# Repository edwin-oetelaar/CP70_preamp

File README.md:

# Yamaha CP70 Electric Grand Piano - 72 Channel Pre-amplifier Project

https://www.pomeindhoven.nl/

Paviljoen Ongehoorde Muziek
Vestdijk 25 - 5611 CA
Eindhoven

## Project Overview

This repository contains the KiCad project files, documentation, and design decisions for a custom-built 72-channel pre-amplifier designed for a Yamaha CP70 electric grand piano. This project is an open-source initiative developed in collaboration with [Paviljoen Ongehoorde Muziek (POM)](https://www.pomeindhoven.nl/) in Eindhoven, Netherlands, as part of an art project.

The primary goal of this pre-amplifier is to individually buffer and potentially amplify the signals from each of the 72 string pickups of the CP70, providing a high-quality, low-noise output output signal for further amplification to 72 speakers.

**Repository URL:** [https://github.com/edwin-oetelaar/CP70_preamp/tree/main](https://github.com/edwin-oetelaar/CP70_preamp/tree/main)

## Image of the piano

## Background

The Yamaha CP70 is an iconic electric grand piano known for its unique sound, derived from real strings and hammers combined with a piezo pickup system.
This project aims to provide a modern, high-fidelity replacement, with 72 separate output channels as an alternative pre-amplifier system.

This pre-amp is designed with the following considerations:
*   **High Input Impedance:** To accurately capture the full tonal character of the CP70 pickups without loading them down.
*   **Low Noise Performance:** Essential for a clean signal, especially with 72 individual channels.
*   **Sufficient Headroom:** To handle the potentially large signal swings from the pickups.
*   **Individual Channel Processing:** Each pickup receives its own pre-amplifier stage.
*   **Modularity:** For ease of assembly, testing, and maintenance.
*   **Open Source:** All design files and documentation are publicly available to encourage learning, modification, accessibility.

## Project Status

[ **TODO: Update this section regularly, e.g., In Design, Prototyping, Tested, In Use** ]

*   Current Version: [e.g., v0.1 - Initial Design]
*   Key Milestones:
    *   [x] Initial schematic design complete.
    *   [x] PCB layout for [16]-channel module complete.
    *   [x] PCB ordered
    *   [x] parts ordered
    *   [ ] First prototype(s) built and tested.
    *   [ ] Full 72-channel system assembled.
    *   [ ] Integration with the CP70 at Paviljoen Ongehoorde Muziek.

## Design Files and Documentation

This repository is structured to include:

*   **/kicad_project:** Contains the KiCad schematic and PCB layout files.
    *   `CP70_preamp.kicad_pro` - Main KiCad project file.
    *   `CP70_preamp.kicad_sch` - Main schematic file.
    *   `CP70_preamp.kicad_pcb` - Main PCB layout file (or individual module files).
    *   `libraries/` - Custom schematic symbols and PCB footprints, if any.
    *   `out1/` - Gerber files for PCB manufacturing (to be added when ready). (file out1.zip sent to JLCPCB)
    *   `bom/` - Bill of Materials (to be added).
*   **/documentation:**
    *   `design_decisions.md` - Detailed explanation of the design choices, component selection, and rationale.
    *   `specifications.md` - Target specifications for the pre-amplifier.
    *   `testing_procedure.md` - (To be added) How to test individual modules and the full system.
    *   Images, block diagrams, and other supporting documents.
*   **/images:** Schematics, photos of prototypes, etc.
*   `README.md` - This file.

# image of version 0.1 printed circuit board

## Key Design Aspects (Summary)

*   **Number of Channels:** 72 (one for each pickup)
*   **Input Stage:** High-impedance buffer for each channel.
    *   Target Input Impedance: 470K Ω
    *   Expected Pickup Output: Up to 45V peak-to-peak in 1 M (requiring input attenuation).
*   **Operational Amplifier:** [e.g., TL072 or similar, specify your choice and link to design_decisions.md]
*   **Power Supply:** Symmetrical (e.g., +/-15V or +/-18V)
*   **Gain:** [e.g., Unity gain buffer, or variable gain via potentiometer - specify and link to design_decisions.md]

More detailed information on architecture, component choices, and trade-offs can be found in `/documentation/design_decisions.md`.

## Getting Started / How to Use

1.  **Clone the repository:**
    ```bash
    git clone https://github.com/edwin-oetelaar/CP70_preamp.git
    cd CP70_preamp
    ```
2.  **Open in KiCad:** Open the `CP70_preamp.kicad_pro` file in KiCad (Latest version).
3.  **Review Schematics and PCB Layout:** Explore the design in the KiCad schematic editor and PCB editor.
4.  **Check Documentation:** Read through the `design_decisions.md` and other documents for a deeper understanding.

## Contributing

This is an open-source project, and contributions or suggestions are welcome! If you have ideas, find bugs, or want to contribute to the design:

1.  **Fork the repository.**
2.  **Create a new branch** for your feature or bug fix.
3.  **Make your changes.**
4.  **Submit a Pull Request** with a clear description of your changes.

You can also open an [Issue](https://github.com/edwin-oetelaar/CP70_preamp/issues) to report bugs or suggest improvements.

## Collaboration

This project is in proud collaboration with:

**Paviljoen Ongehoorde Muziek (POM)**
Vestdijk 25 - 5611 CA Eindhoven
[https://www.pomeindhoven.nl/](https://www.pomeindhoven.nl/)

The pre-amplifier is intended for use in an art project hosted at POM.

## License

This project is licensed under the [MIT License](LICENSE.md) - see the LICENSE.md file for details.

## Contact

For questions or discussions regarding this project, you can contact:
*   Edwin van den Oetelaar - Leave a message in the issue tracker or google my name/email 
*   Or open an issue on this GitHub repository.

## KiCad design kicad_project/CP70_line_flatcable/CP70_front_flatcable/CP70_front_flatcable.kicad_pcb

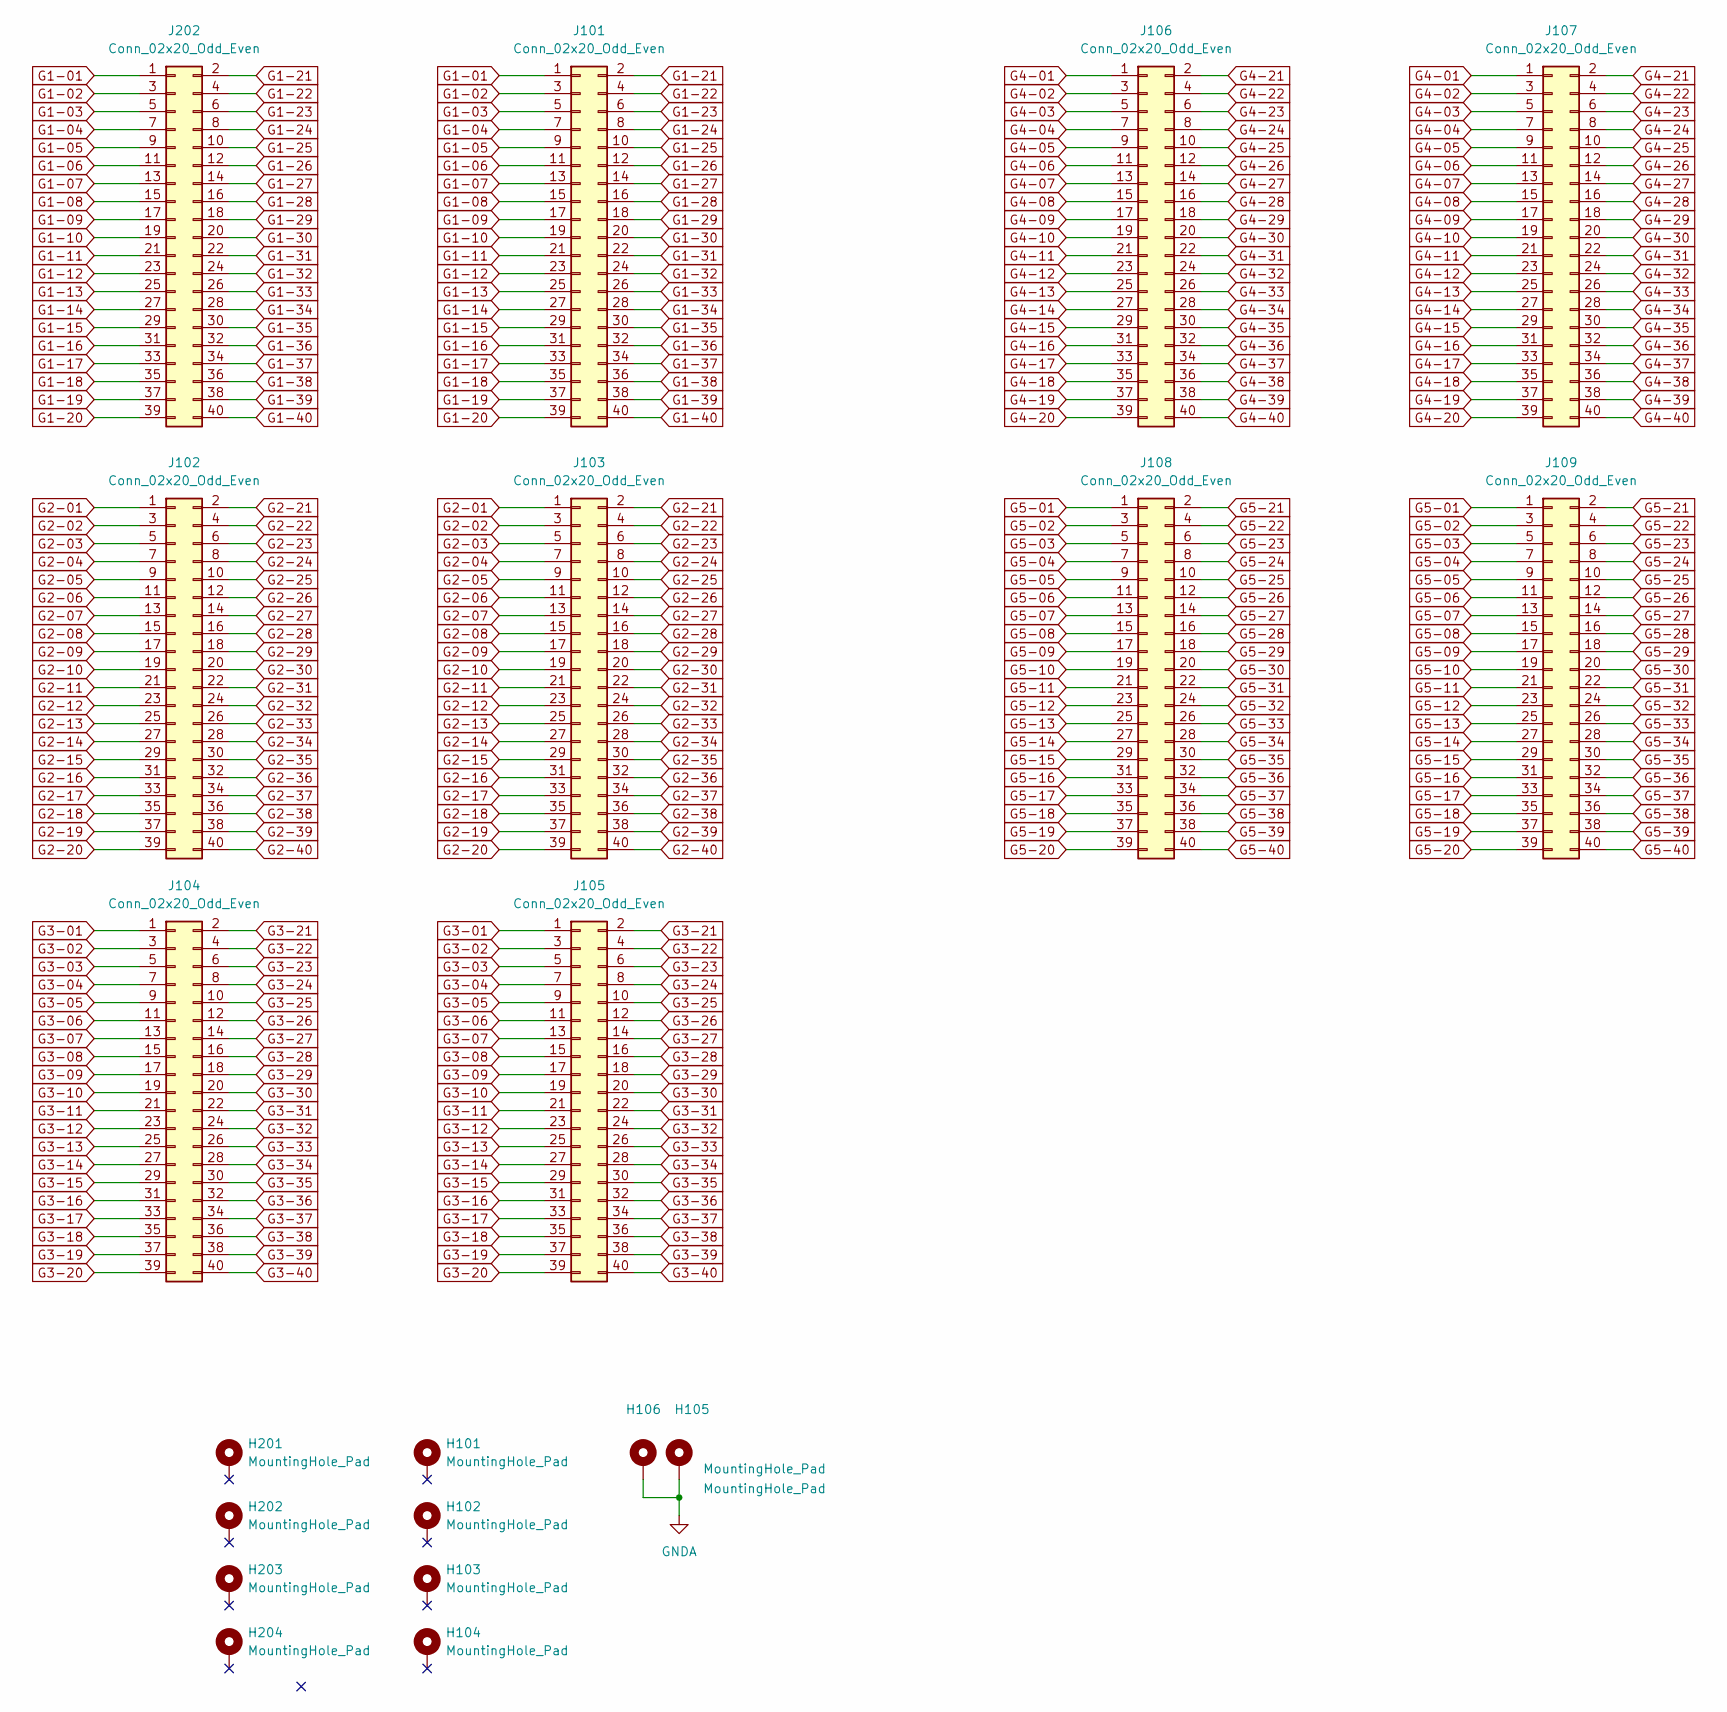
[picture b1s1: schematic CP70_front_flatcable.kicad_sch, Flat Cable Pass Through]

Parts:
H101, H102, H103, H104, H105, H106, H201, H202, H203, H204: MountingHole_Pad; MountingHole_3.2mm_M3_Pad_Via
J101, J102, J103, J104, J105, J106, J107, J108, J109, J202: Conn_02x20_Odd_Even; IDC-Header_2x20-1MP_P2.54mm_Latch9.5mm_Vertical

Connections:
G1-01: J101.1, J202.1
G1-02: J101.3, J202.3
G1-03: J101.5, J202.5
G1-04: J101.7, J202.7
G1-05: J101.9, J202.9
G1-06: J101.11, J202.11
G1-07: J101.13, J202.13
G1-08: J101.15, J202.15
G1-09: J101.17, J202.17
G1-10: J101.19, J202.19
G1-11: J101.21, J202.21
G1-12: J101.23, J202.23
G1-13: J101.25, J202.25
G1-14: J101.27, J202.27
G1-15: J101.29, J202.29
G1-16: J101.31, J202.31
G1-17: J101.33, J202.33
G1-18: J101.35, J202.35
G1-19: J101.37, J202.37
G1-20: J101.39, J202.39
G1-21: J101.2, J202.2
G1-22: J101.4, J202.4
G1-23: J101.6, J202.6
G1-24: J101.8, J202.8
G1-25: J101.10, J202.10
G1-26: J101.12, J202.12
G1-27: J101.14, J202.14
G1-28: J101.16, J202.16
G1-29: J101.18, J202.18
G1-30: J101.20, J202.20
G1-31: J101.22, J202.22
G1-32: J101.24, J202.24
G1-33: J101.26, J202.26
G1-34: J101.28, J202.28
G1-35: J101.30, J202.30
G1-36: J101.32, J202.32
G1-37: J101.34, J202.34
G1-38: J101.36, J202.36
G1-39: J101.38, J202.38
G1-40: J101.40, J202.40
G2-01: J102.1, J103.1
G2-02: J102.3, J103.3
G2-03: J102.5, J103.5
G2-04: J102.7, J103.7
G2-05: J102.9, J103.9
G2-06: J102.11, J103.11
G2-07: J102.13, J103.13
G2-08: J102.15, J103.15
G2-09: J102.17, J103.17
G2-10: J102.19, J103.19
G2-11: J102.21, J103.21
G2-12: J102.23, J103.23
G2-13: J102.25, J103.25
G2-14: J102.27, J103.27
G2-15: J102.29, J103.29
G2-16: J102.31, J103.31
G2-17: J102.33, J103.33
G2-18: J102.35, J103.35
G2-19: J102.37, J103.37
G2-20: J102.39, J103.39
G2-21: J102.2, J103.2
G2-22: J102.4, J103.4
G2-23: J102.6, J103.6
G2-24: J102.8, J103.8
G2-25: J102.10, J103.10
G2-26: J102.12, J103.12
G2-27: J102.14, J103.14
G2-28: J102.16, J103.16
G2-29: J102.18, J103.18
G2-30: J102.20, J103.20
G2-31: J102.22, J103.22
G2-32: J102.24, J103.24
G2-33: J102.26, J103.26
G2-34: J102.28, J103.28
G2-35: J102.30, J103.30
G2-36: J102.32, J103.32
G2-37: J102.34, J103.34
G2-38: J102.36, J103.36
G2-39: J102.38, J103.38
G2-40: J102.40, J103.40
G3-01: J104.1, J105.1
G3-02: J104.3, J105.3
G3-03: J104.5, J105.5
G3-04: J104.7, J105.7
G3-05: J104.9, J105.9
G3-06: J104.11, J105.11
G3-07: J104.13, J105.13
G3-08: J104.15, J105.15
G3-09: J104.17, J105.17
G3-10: J104.19, J105.19
G3-11: J104.21, J105.21
G3-12: J104.23, J105.23
G3-13: J104.25, J105.25
G3-14: J104.27, J105.27
G3-15: J104.29, J105.29
G3-16: J104.31, J105.31
G3-17: J104.33, J105.33
G3-18: J104.35, J105.35
G3-19: J104.37, J105.37
G3-20: J104.39, J105.39
G3-21: J104.2, J105.2
G3-22: J104.4, J105.4
G3-23: J104.6, J105.6
G3-24: J104.8, J105.8
G3-25: J104.10, J105.10
G3-26: J104.12, J105.12
G3-27: J104.14, J105.14
G3-28: J104.16, J105.16
G3-29: J104.18, J105.18
G3-30: J104.20, J105.20
G3-31: J104.22, J105.22
G3-32: J104.24, J105.24
G3-33: J104.26, J105.26
G3-34: J104.28, J105.28
G3-35: J104.30, J105.30
G3-36: J104.32, J105.32
G3-37: J104.34, J105.34
G3-38: J104.36, J105.36
G3-39: J104.38, J105.38
G3-40: J104.40, J105.40
G4-01: J106.1, J107.1
G4-02: J106.3, J107.3
G4-03: J106.5, J107.5
G4-04: J106.7, J107.7
G4-05: J106.9, J107.9
G4-06: J106.11, J107.11
G4-07: J106.13, J107.13
G4-08: J106.15, J107.15
G4-09: J106.17, J107.17
G4-10: J106.19, J107.19
G4-11: J106.21, J107.21
G4-12: J106.23, J107.23
G4-13: J106.25, J107.25
G4-14: J106.27, J107.27
G4-15: J106.29, J107.29
G4-16: J106.31, J107.31
G4-17: J106.33, J107.33
G4-18: J106.35, J107.35
G4-19: J106.37, J107.37
G4-20: J106.39, J107.39
G4-21: J106.2, J107.2
G4-22: J106.4, J107.4
G4-23: J106.6, J107.6
G4-24: J106.8, J107.8
G4-25: J106.10, J107.10
G4-26: J106.12, J107.12
G4-27: J106.14, J107.14
G4-28: J106.16, J107.16
G4-29: J106.18, J107.18
G4-30: J106.20, J107.20
G4-31: J106.22, J107.22
G4-32: J106.24, J107.24
G4-33: J106.26, J107.26
G4-34: J106.28, J107.28
G4-35: J106.30, J107.30
G4-36: J106.32, J107.32
G4-37: J106.34, J107.34
G4-38: J106.36, J107.36
G4-39: J106.38, J107.38
G4-40: J106.40, J107.40
G5-01: J108.1, J109.1
G5-02: J108.3, J109.3
G5-03: J108.5, J109.5
G5-04: J108.7, J109.7
G5-05: J108.9, J109.9
G5-06: J108.11, J109.11
G5-07: J108.13, J109.13
G5-08: J108.15, J109.15
G5-09: J108.17, J109.17
G5-10: J108.19, J109.19
G5-11: J108.21, J109.21
G5-12: J108.23, J109.23
G5-13: J108.25, J109.25
G5-14: J108.27, J109.27
G5-15: J108.29, J109.29
G5-16: J108.31, J109.31
G5-17: J108.33, J109.33
G5-18: J108.35, J109.35
G5-19: J108.37, J109.37
G5-20: J108.39, J109.39
G5-21: J108.2, J109.2
G5-22: J108.4, J109.4
G5-23: J108.6, J109.6
G5-24: J108.8, J109.8
G5-25: J108.10, J109.10
G5-26: J108.12, J109.12
G5-27: J108.14, J109.14
G5-28: J108.16, J109.16
G5-29: J108.18, J109.18
G5-30: J108.20, J109.20
G5-31: J108.22, J109.22
G5-32: J108.24, J109.24
G5-33: J108.26, J109.26
G5-34: J108.28, J109.28
G5-35: J108.30, J109.30
G5-36: J108.32, J109.32
G5-37: J108.34, J109.34
G5-38: J108.36, J109.36
G5-39: J108.38, J109.38
G5-40: J108.40, J109.40
GNDA: H105.1, H106.1

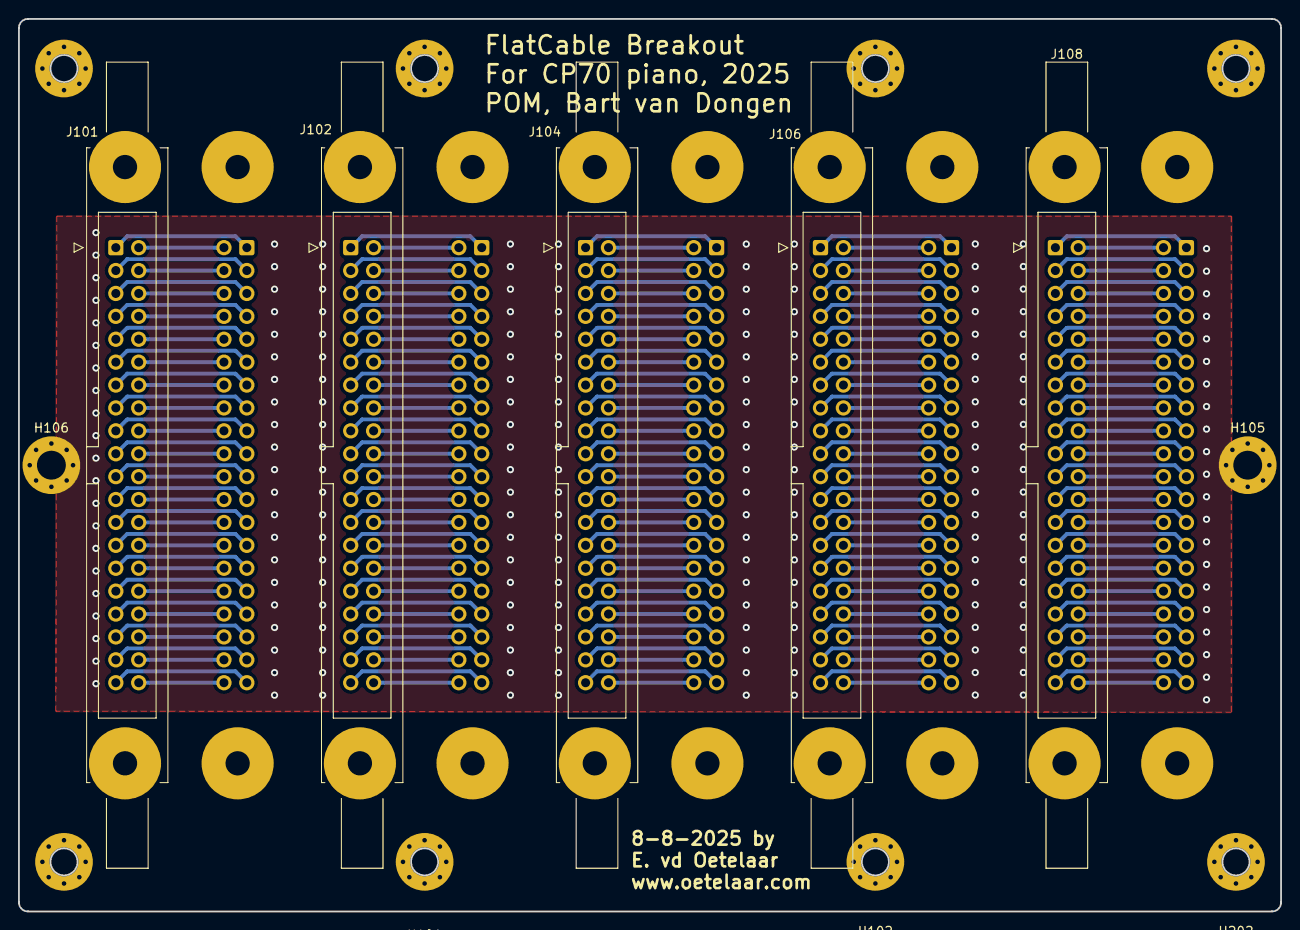
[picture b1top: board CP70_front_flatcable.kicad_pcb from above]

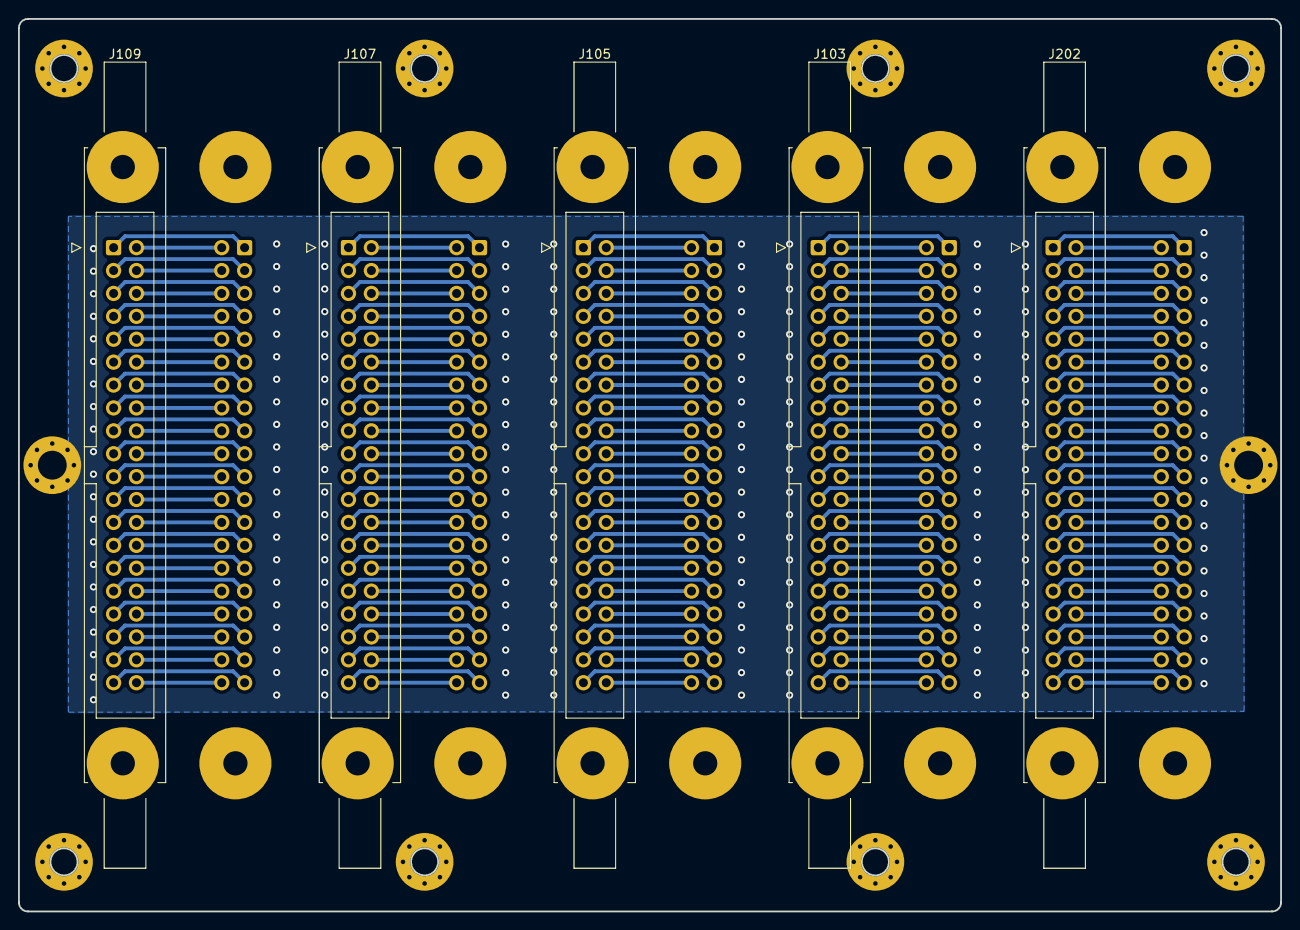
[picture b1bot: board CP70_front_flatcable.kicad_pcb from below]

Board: 2 copper layers, 140.0 x 99.0 mm, 20 parts (5 on the bottom side), 201 nets.

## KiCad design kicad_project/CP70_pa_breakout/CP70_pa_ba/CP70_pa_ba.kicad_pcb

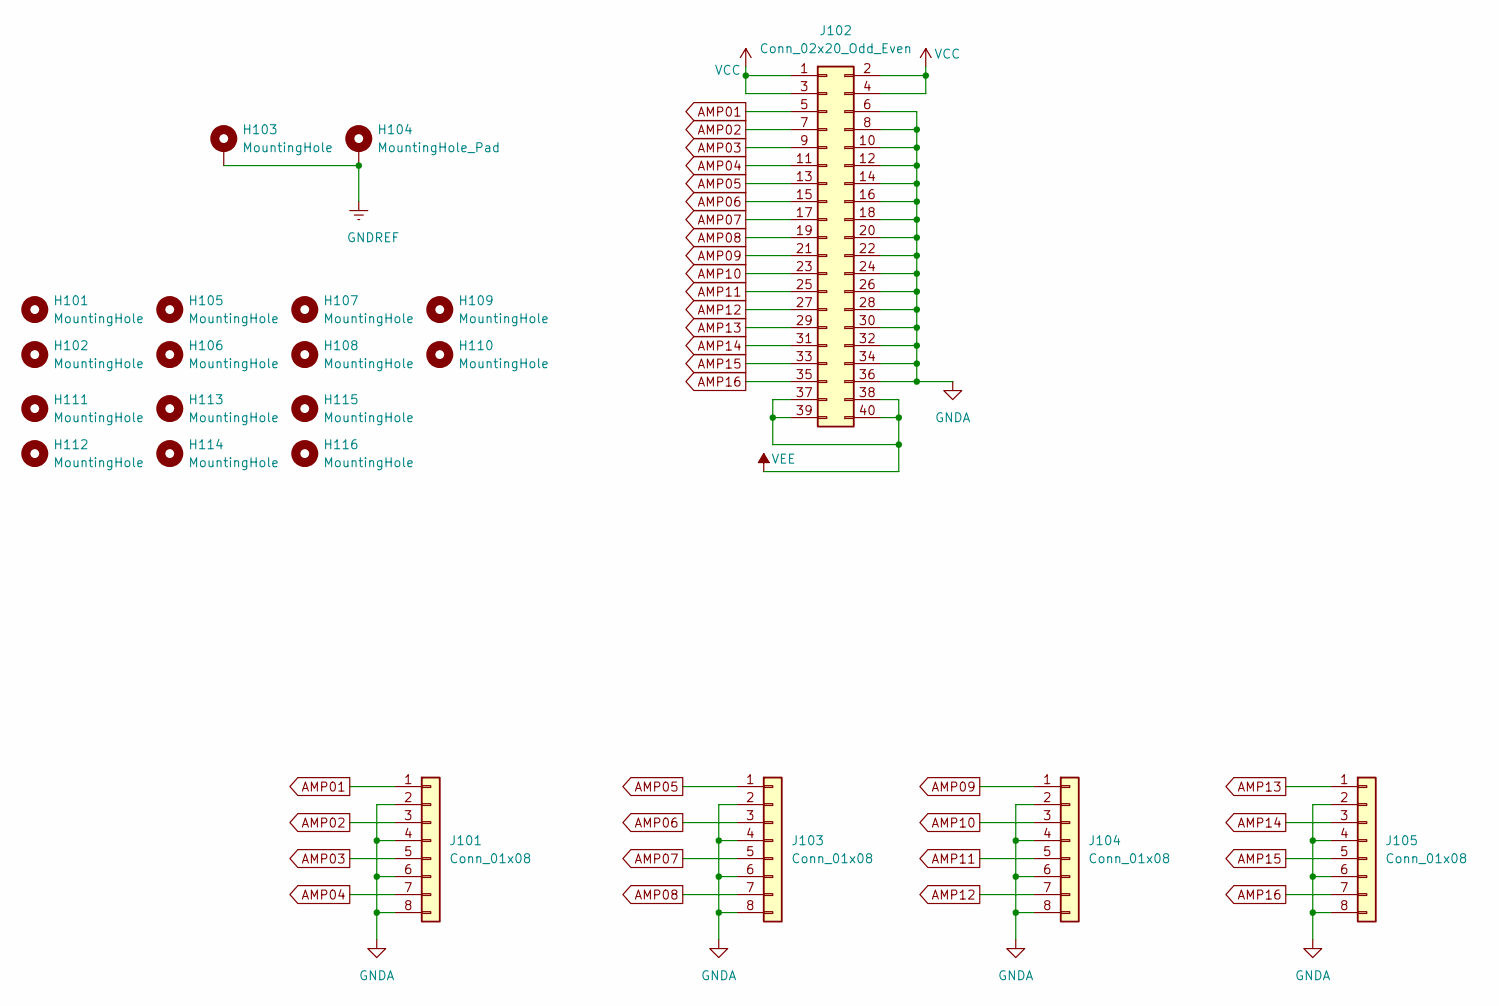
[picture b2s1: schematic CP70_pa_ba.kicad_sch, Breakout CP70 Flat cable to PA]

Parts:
H101, H102, H103, H105, H106, H107, H108, H109, H110, H111, H112, H113, H114, H115, H116: MountingHole; MountingHole_3.2mm_M3_Pad_Via
H104: MountingHole_Pad; MountingHole_3.2mm_M3_Pad_Via
J101, J103, J104, J105: Conn_01x08; KF141R-2.54-8
J102: Conn_02x20_Odd_Even; IDC-Header_2x20_P2.54mm_Latch_Vertical

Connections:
AMP01: J101.1, J102.5
AMP02: J101.3, J102.7
AMP03: J101.5, J102.9
AMP04: J101.7, J102.11
AMP05: J102.13, J103.1
AMP06: J102.15, J103.3
AMP07: J102.17, J103.5
AMP08: J102.19, J103.7
AMP09: J102.21, J104.1
AMP10: J102.23, J104.3
AMP11: J102.25, J104.5
AMP12: J102.27, J104.7
AMP13: J102.29, J105.1
AMP14: J102.31, J105.3
AMP15: J102.33, J105.5
AMP16: J102.35, J105.7
GNDA: J101.2, J101.4, J101.6, J101.8, J102.6, J102.8, J102.10, J102.12, J102.14, J102.16, J102.18, J102.20, J102.22, J102.24, J102.26, J102.28, J102.30, J102.32, J102.34, J102.36, J103.2, J103.4, J103.6, J103.8, J104.2, J104.4, J104.6, J104.8, J105.2, J105.4, J105.6, J105.8
GNDREF: H103.1, H104.1
VCC: J102.1, J102.2, J102.3, J102.4
VEE: J102.37, J102.38, J102.39, J102.40

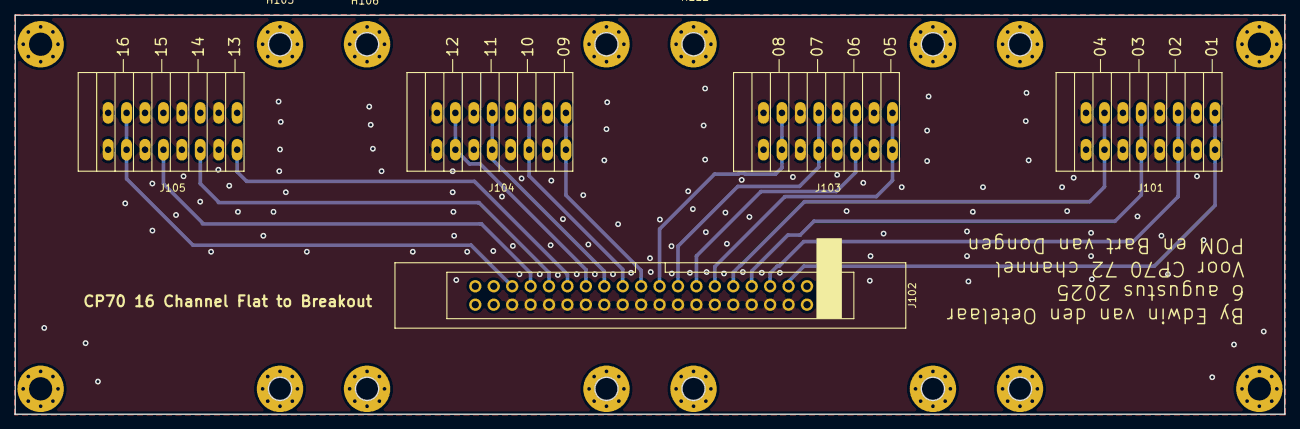
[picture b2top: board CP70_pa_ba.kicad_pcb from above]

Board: 2 copper layers, 175.0 x 55.0 mm, 21 parts (0 on the bottom side), 20 nets.

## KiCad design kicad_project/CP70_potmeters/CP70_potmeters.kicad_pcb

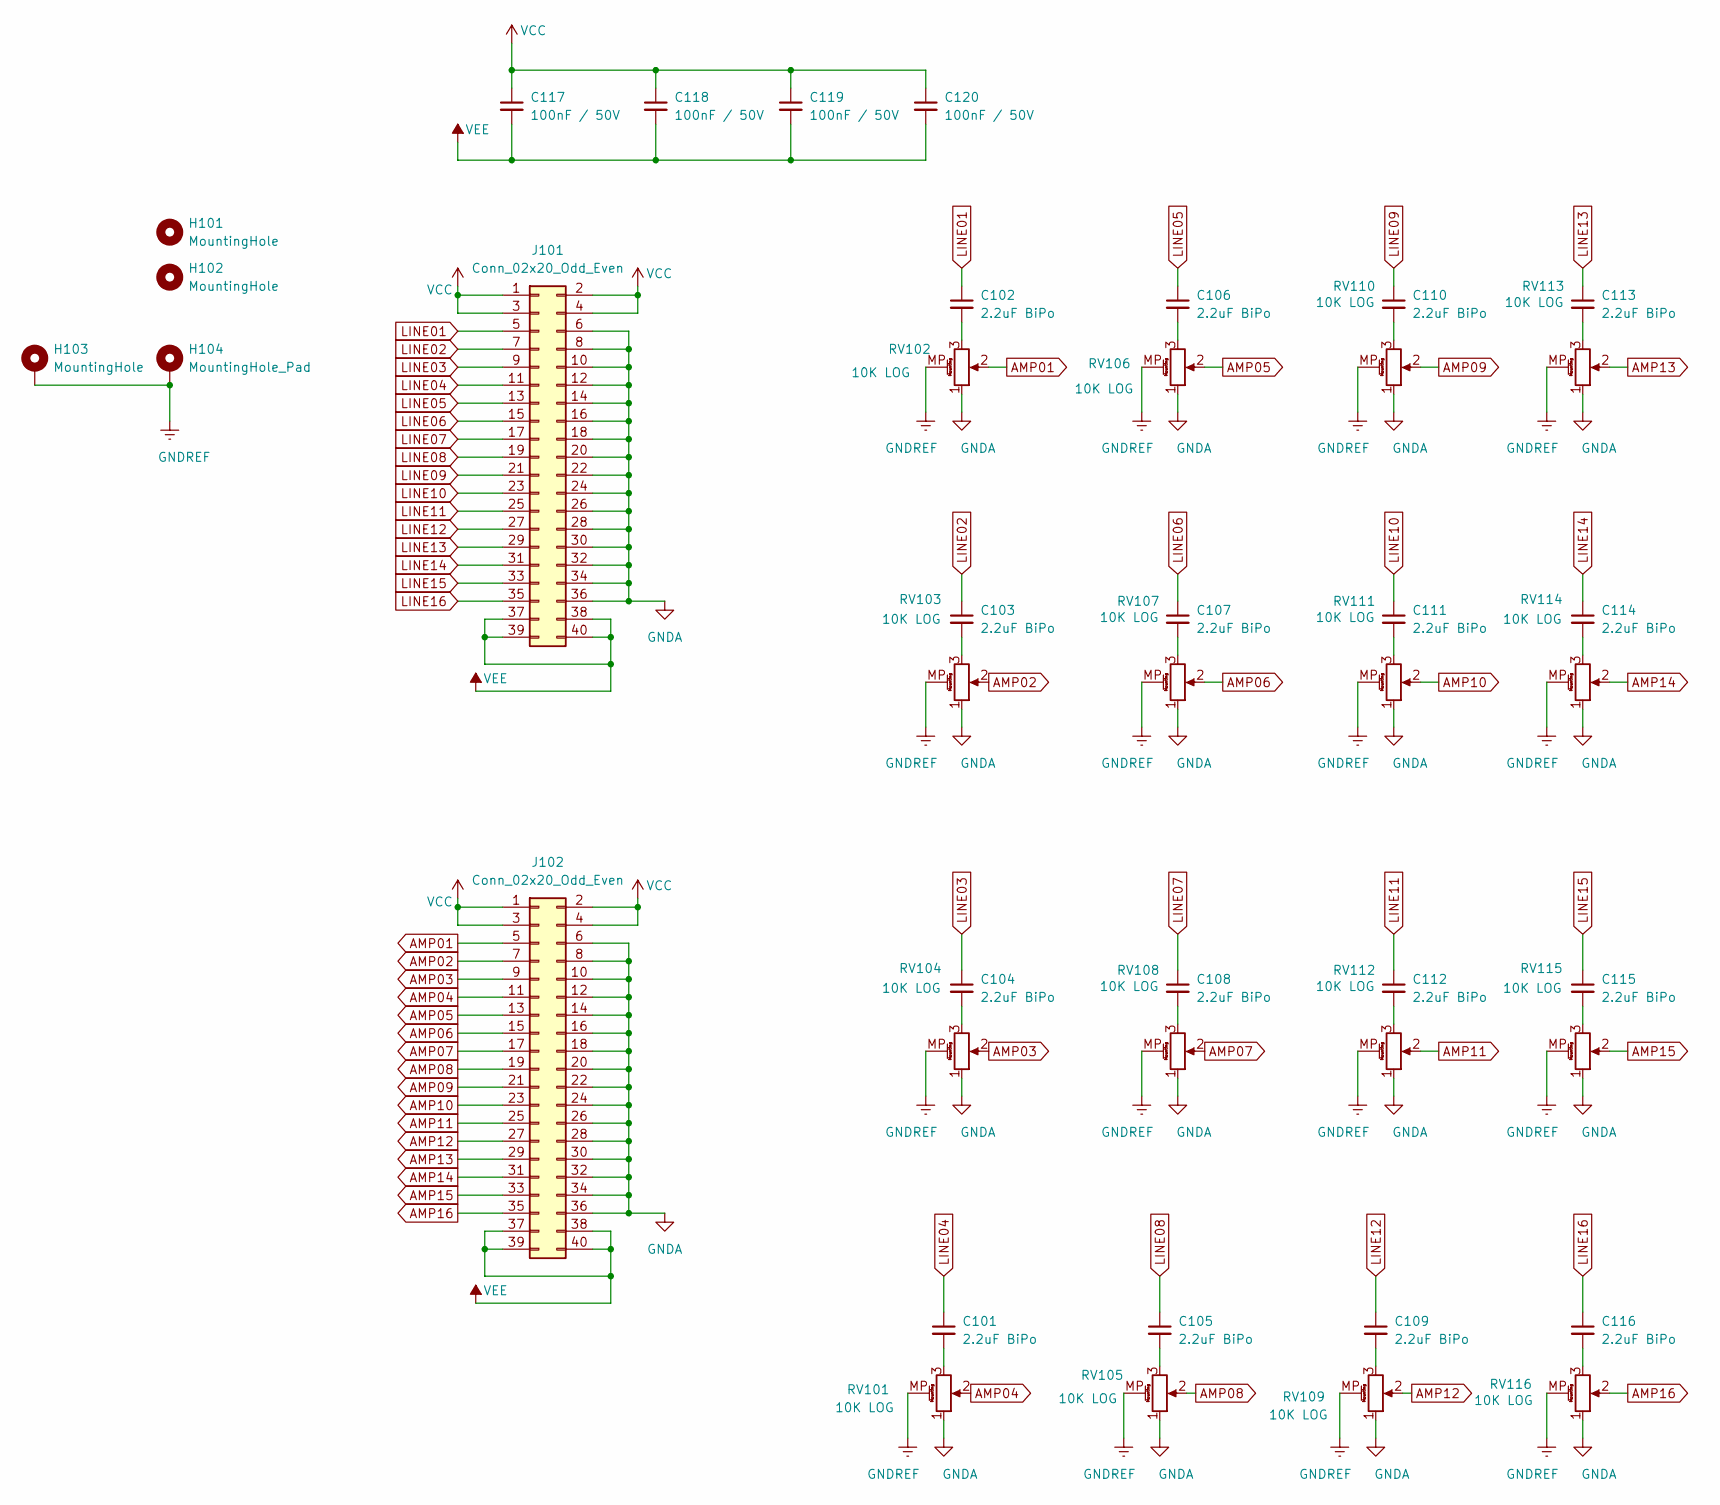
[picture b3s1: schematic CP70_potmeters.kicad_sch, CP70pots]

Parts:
C101, C102, C103, C104, C105, C106, C107, C108, C109, C110, C111, C112, C113, C114, C115, C116: 2.2uF BiPo; C_Radial_D5.0mm_H11.0mm_P2.00mm
C117, C118, C119, C120: 100nF / 50V; C_Disc_D6.0mm_W2.5mm_P5.00mm
H101, H102, H103: MountingHole; MountingHole_3.2mm_M3_Pad_Via
H104: MountingHole_Pad; MountingHole_3.2mm_M3_Pad_Via
J101, J102: Conn_02x20_Odd_Even; IDC-Header_2x20_P2.54mm_Latch_Vertical
RV101, RV102, RV103, RV104, RV105, RV106, RV107, RV108, RV109, RV110, RV111, RV112, RV113, RV114, RV115, RV116: 10K LOG; Potentiometer_Alps_RK09L_Single_Horizontal

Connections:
AMP01: J102.5, RV102.2
AMP02: J102.7, RV103.2
AMP03: J102.9, RV104.2
AMP04: J102.11, RV101.2
AMP05: J102.13, RV106.2
AMP06: J102.15, RV107.2
AMP07: J102.17, RV108.2
AMP08: J102.19, RV105.2
AMP09: J102.21, RV110.2
AMP10: J102.23, RV111.2
AMP11: J102.25, RV112.2
AMP12: J102.27, RV109.2
AMP13: J102.29, RV113.2
AMP14: J102.31, RV114.2
AMP15: J102.33, RV115.2
AMP16: J102.35, RV116.2
GNDA: J101.6, J101.8, J101.10, J101.12, J101.14, J101.16, J101.18, J101.20, J101.22, J101.24, J101.26, J101.28, J101.30, J101.32, J101.34, J101.36, J102.6, J102.8, J102.10, J102.12, J102.14, J102.16, J102.18, J102.20, J102.22, J102.24, J102.26, J102.28, J102.30, J102.32, J102.34, J102.36, RV101.1, RV102.1, RV103.1, RV104.1, RV105.1, RV106.1, RV107.1, RV108.1, RV109.1, RV110.1, RV111.1, RV112.1, RV113.1, RV114.1, RV115.1, RV116.1
GNDREF: H103.1, H104.1, RV101.MP (MountPin), RV102.MP (MountPin), RV103.MP (MountPin), RV104.MP (MountPin), RV105.MP (MountPin), RV106.MP (MountPin), RV107.MP (MountPin), RV108.MP (MountPin), RV109.MP (MountPin), RV110.MP (MountPin), RV111.MP (MountPin), RV112.MP (MountPin), RV113.MP (MountPin), RV114.MP (MountPin), RV115.MP (MountPin), RV116.MP (MountPin)
LINE01: C102.1, J101.5
LINE02: C103.1, J101.7
LINE03: C104.1, J101.9
LINE04: C101.1, J101.11
LINE05: C106.1, J101.13
LINE06: C107.1, J101.15
LINE07: C108.1, J101.17
LINE08: C105.1, J101.19
LINE09: C110.1, J101.21
LINE10: C111.1, J101.23
LINE11: C112.1, J101.25
LINE12: C109.1, J101.27
LINE13: C113.1, J101.29
LINE14: C114.1, J101.31
LINE15: C115.1, J101.33
LINE16: C116.1, J101.35
unnamed: C101.2, RV101.3
unnamed: C102.2, RV102.3
unnamed: C103.2, RV103.3
unnamed: C104.2, RV104.3
unnamed: C105.2, RV105.3
unnamed: C106.2, RV106.3
unnamed: C107.2, RV107.3
unnamed: C108.2, RV108.3
unnamed: C109.2, RV109.3
unnamed: C110.2, RV110.3
unnamed: C111.2, RV111.3
unnamed: C112.2, RV112.3
unnamed: C113.2, RV113.3
unnamed: C114.2, RV114.3
unnamed: C115.2, RV115.3
unnamed: C116.2, RV116.3
VCC: C117.1, C118.1, C119.1, C120.1, J101.1, J101.2, J101.3, J101.4, J102.1, J102.2, J102.3, J102.4
VEE: C117.2, C118.2, C119.2, C120.2, J101.37, J101.38, J101.39, J101.40, J102.37, J102.38, J102.39, J102.40

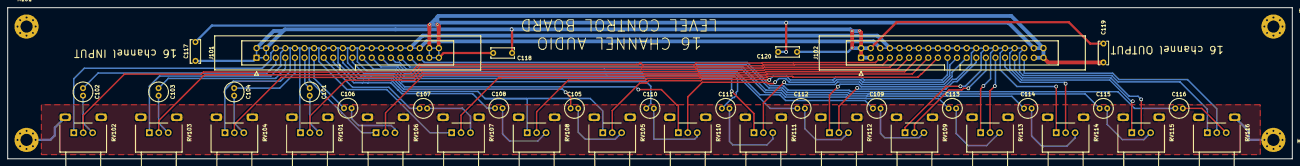
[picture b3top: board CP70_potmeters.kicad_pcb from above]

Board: 2 copper layers, 340.0 x 40.0 mm, 42 parts (0 on the bottom side), 52 nets.
